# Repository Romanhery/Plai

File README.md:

# Plai-Hackpad
Plai is a 3x3 key macropad with a rotary encoder, an OLED Display. It uses KMK firmware
I made this so that I can learn PCB design, CAD, and Programming. It has upgraded and helped me with my experience.
# Features:
<ul>
   <li>128x32 OLED Display to show a cool message</li>
   <li>EC11 Rotary encoder to change volume</li>
   <li>9 keys for the shorcuts and media control</li>
</ul>
# PCB:
   <h2>Schematic</h2>
   
   <h2>PCB</h2>
   
   <p>Made in <a href="https://www.kicad.org/">Ki-CAD</a></p> 

# CAD:
   <p>Everything is held together by using 5 M3 Bolts and heat inserts.</p>
   <p>It has 2 printed pieces to cover the electronics and house them.</p>
   <p>Made in Fusion 360</p>

# Firmware:
   <p>Made with <a href="https://github.com/KMKfw/kmk_firmware">KMK</a> firmware</p> 
   <h3>Features</h3>
   <li>Volume control if you twist the rotary encoder and if you press the encoder to mute</li>
   <li>Screen displays cool message</li>
   <li>They have macros for any shorcut you want (I have those right now for me)</li>
   
# BOM:
<p>Everything you need to make this macro pad is here!</p>
<ul>
    <li>9x Cherry MX Switches</li>
    <li>9x DSA Keycaps</li>
    <li>5x M3x5x4 Heatset inserts</li>
    <li>4x M3x16mm SHCS Bolts</li>
    <li>9x 1N4148 DO-35 Diodes.</li>
    <li>1x 0.91" OLED Display</li>
    <li>1x EC11 Rotary Encoder</li>
    <li>1x XIAO RP2040</li>
    <li>1x Case (2 printed parts)</li>
   <a href="https://docs.google.com/spreadsheets/d/1uIeMTGPOrdSAiFDxR4G393WpXhlTQVRrd_AwqsaPwl4/edit?usp=sharing">BOM HERE WITH LINKS</a>
</ul>
## Acknowledgements

* [Orpheuspad](https://github.com/hackclub/hackpad/tree/main/cad/orpheuspad)
* [Keybie](https://github.com/Mirai-09/Keybie-Hackpads)
## Authors
- [@Romanhery](https://github.com/Romanhery)

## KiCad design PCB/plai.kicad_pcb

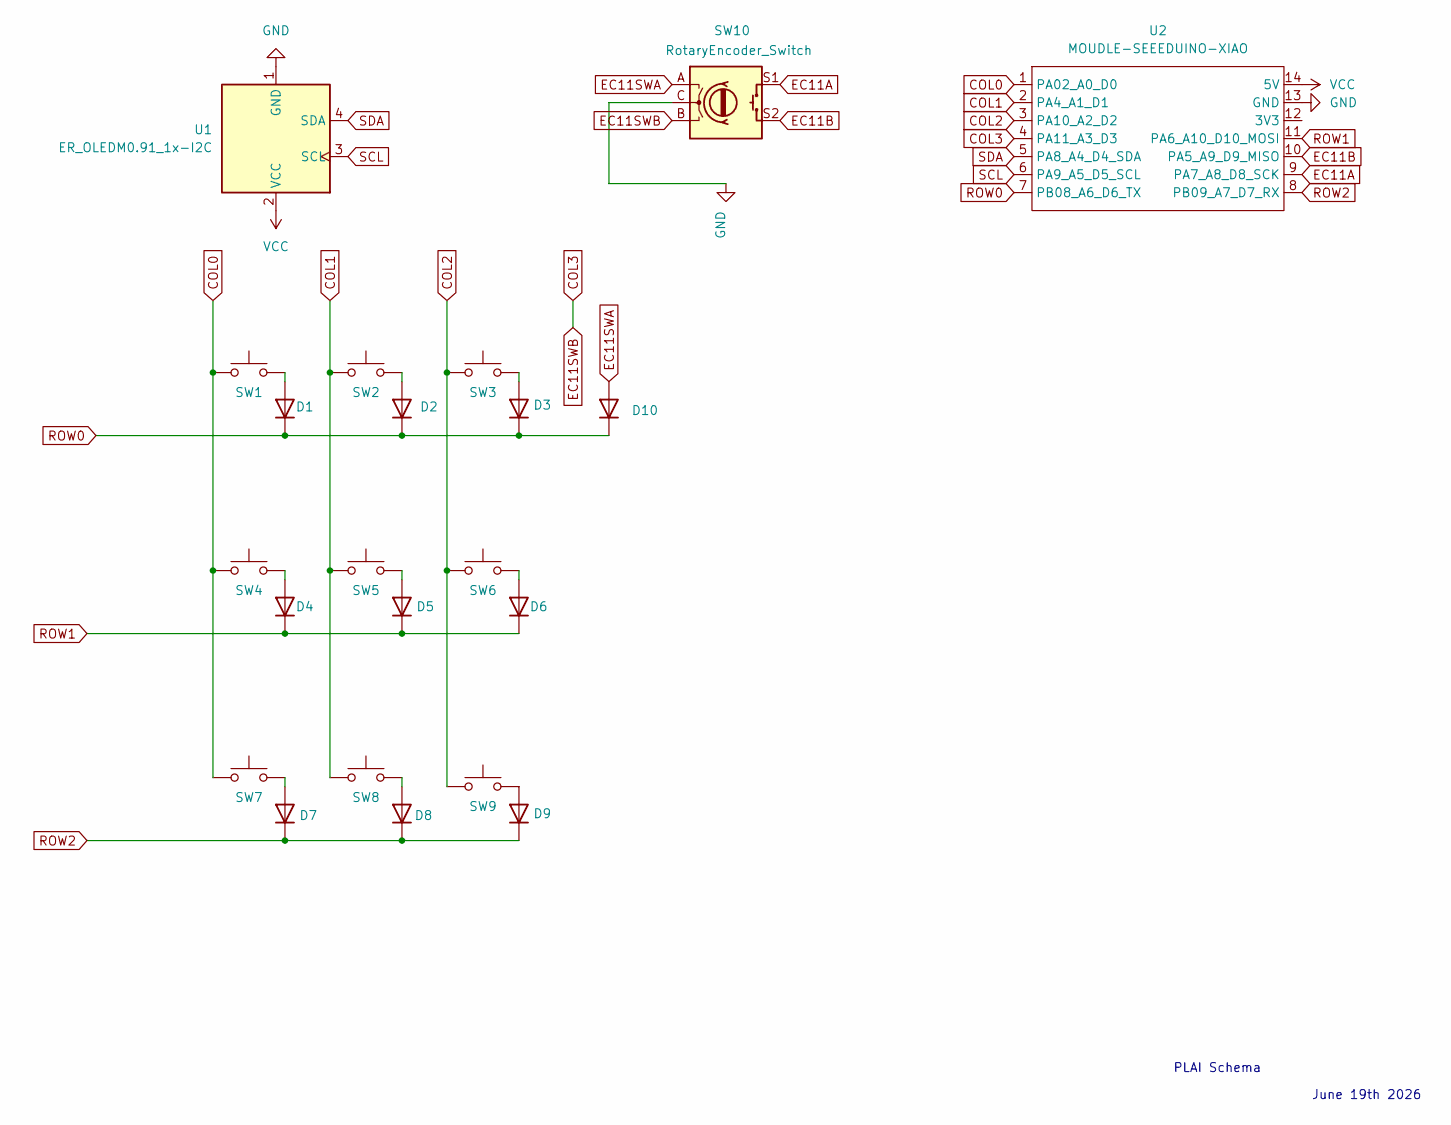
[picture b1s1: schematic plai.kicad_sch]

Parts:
D1, D2, D3, D4, D5, D6, D7, D8, D9, D10: 1N4148; D_DO-35_SOD27_P7.62mm_Horizontal
SW1, SW2, SW3, SW4, SW5, SW6, SW7, SW8, SW9: SW_Push; SW_Cherry_MX_1.00u_PCB
SW10: RotaryEncoder_Switch; RotaryEncoder_Alps_EC11E-Switch_Vertical_H20mm
U1: ER_OLEDM0.91_1x-I2C
U2: MOUDLE-SEEEDUINO-XIAO; XIAO-Generic-Hybrid-14P-2.54-21X17.8MM

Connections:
COL0: SW1.1, SW4.1, SW7.1, U2.1 (PA02_A0_D0)
COL1: SW2.1, SW5.1, SW8.1, U2.2 (PA4_A1_D1)
COL2: SW3.1, SW6.1, SW9.1, U2.3 (PA10_A2_D2)
COL3: SW10.B, U2.4 (PA11_A3_D3)
EC11A: SW10.S1, U2.9 (PA7_A8_D8_SCK)
EC11B: SW10.S2, U2.10 (PA5_A9_D9_MISO)
EC11SWA: D10.2 (A), SW10.A
GND: SW10.C, U1.1 (GND), U2.13 (GND)
unnamed: D1.2 (A), SW1.2
unnamed: D2.2 (A), SW2.2
unnamed: D3.2 (A), SW3.2
unnamed: D4.2 (A), SW4.2
unnamed: D5.2 (A), SW5.2
unnamed: D6.2 (A), SW6.2
unnamed: D7.2 (A), SW7.2
unnamed: D8.2 (A), SW8.2
unnamed: D9.2 (A), SW9.2
ROW0: D1.1 (K), D2.1 (K), D3.1 (K), D10.1 (K), U2.7 (PB08_A6_D6_TX)
ROW1: D4.1 (K), D5.1 (K), D6.1 (K), U2.11 (PA6_A10_D10_MOSI)
ROW2: D7.1 (K), D8.1 (K), D9.1 (K), U2.8 (PB09_A7_D7_RX)
SCL: U1.3 (SCL), U2.6 (PA9_A5_D5_SCL)
SDA: U1.4 (SDA), U2.5 (PA8_A4_D4_SDA)
VCC: U1.2 (VCC), U2.14 (5V)

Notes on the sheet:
PLAI Schema
June 19th 2026

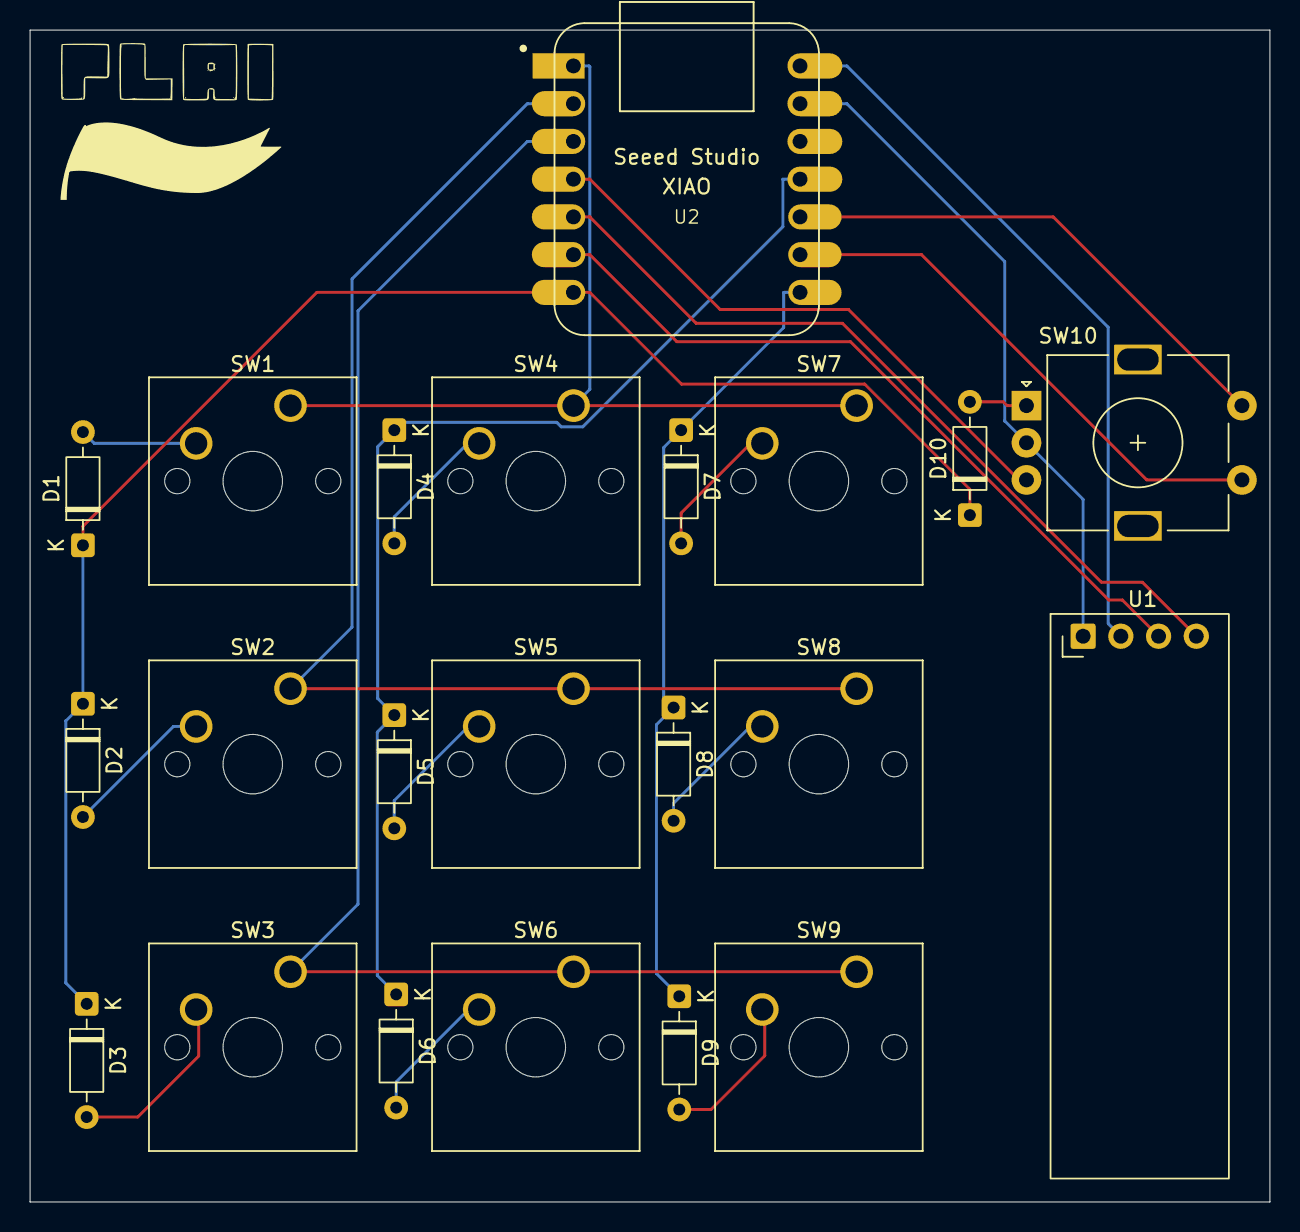
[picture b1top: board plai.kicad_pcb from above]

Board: 2 copper layers, 83.4 x 78.9 mm, 22 parts (0 on the bottom side), 23 nets.

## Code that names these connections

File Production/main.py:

"""
Plai MacroPad

Roman
"""
print("Starting")

#Libraries
import board

from kmk.kmk_keyboard import KMKKeyboard
from kmk.keys import KC
from kmk.scanners import DiodeOrientation
from kmk.modules.encoder import EncoderHandler
from kmk.extensions.display import Display , TextEntry
from kmk.extensions.display.ssd1306 import SSD1306
from kmk.extensions.media_keys import MediaKeys

#Pin Definitons
COL0 = board.D0
COL1 = board.D1
COL2 = board.D2
COL3 = board.D3
SDA = board.D4
SCL = board.D5
ROW0 = board.D6
ROW1 = board.D10
ROW2 = board.D7
EC11B = board.D9
EC11A = board.D8

keyboard = KMKKeyboard()

#Maping out the rows and the collums and what orientation the diodes are
keyboard.col_pins = (COL0,COL1,COL2,COL3)
keyboard.row_pins = (ROW0,ROW1,ROW2)
keyboard.diode_orientation = DiodeOrientation.COL2ROW

encoder_handler = EncoderHandler()


#just adding the modules to the keyboard
keyboard.modules.append(encoder_handler)
keyboard.extensions.append(MediaKeys())

#Maping out the pins and the keys of the encoder
encoder_handler.pins = ((EC11A, EC11B, None, False),)
encoder_handler.map = (((KC.VOLD, KC.VOLU),),)

#mapping out all of the keys
keyboard.keymap = [
    [
        #Row 0
        KC.MPRV, #Previous Song
        KC.MPLY, #Play the Song
        KC.MNXT,  #Next Song
        KC.MUTE, #Mute Song

        #Row 1
        KC.LCTRL(KC.LALT(KC.LCMD(KC.LSHIFT(KC.V)))), # Vscode
        KC.LCTRL(KC.LALT(KC.LCMD(KC.LSHIFT(KC.F)))), # Fusion
        KC.LCTRL(KC.LALT(KC.LCMD(KC.LSHIFT(KC.D)))), # Davionci Resolve
        KC.NO,        # Empty matrix slot: We did this because the encoder doesnt have its own pin and we connected it to the matrix

        # ROW 2
        KC.LCTRL(KC.LALT(KC.LCMD(KC.LSHIFT(KC.K)))), # Ki Cad
        KC.LCTRL(KC.LALT(KC.LCMD(KC.LSHIFT(KC.C)))), # Chrome
        KC.LCTRL(KC.LALT(KC.LCMD(KC.LSHIFT(KC.F12)))),# Finder
        KC.NO,        # Empty matrix slot
    ]
]

#displays Coding Is Awesome!!!
display = Display(
    #Pin maping
    display=SSD1306(sda=SDA,scl=SCL),
    #What should go into the display
    entries=[
        #The actual text Coding is awesome
        TextEntry(text='Coding Is Awesome!!!')
    ],
    #how tall it should be
    height=32
)
#enter it into the actual display and show it
keyboard.extensions.append(display)

if __name__ == '__main__':
    keyboard.go()
